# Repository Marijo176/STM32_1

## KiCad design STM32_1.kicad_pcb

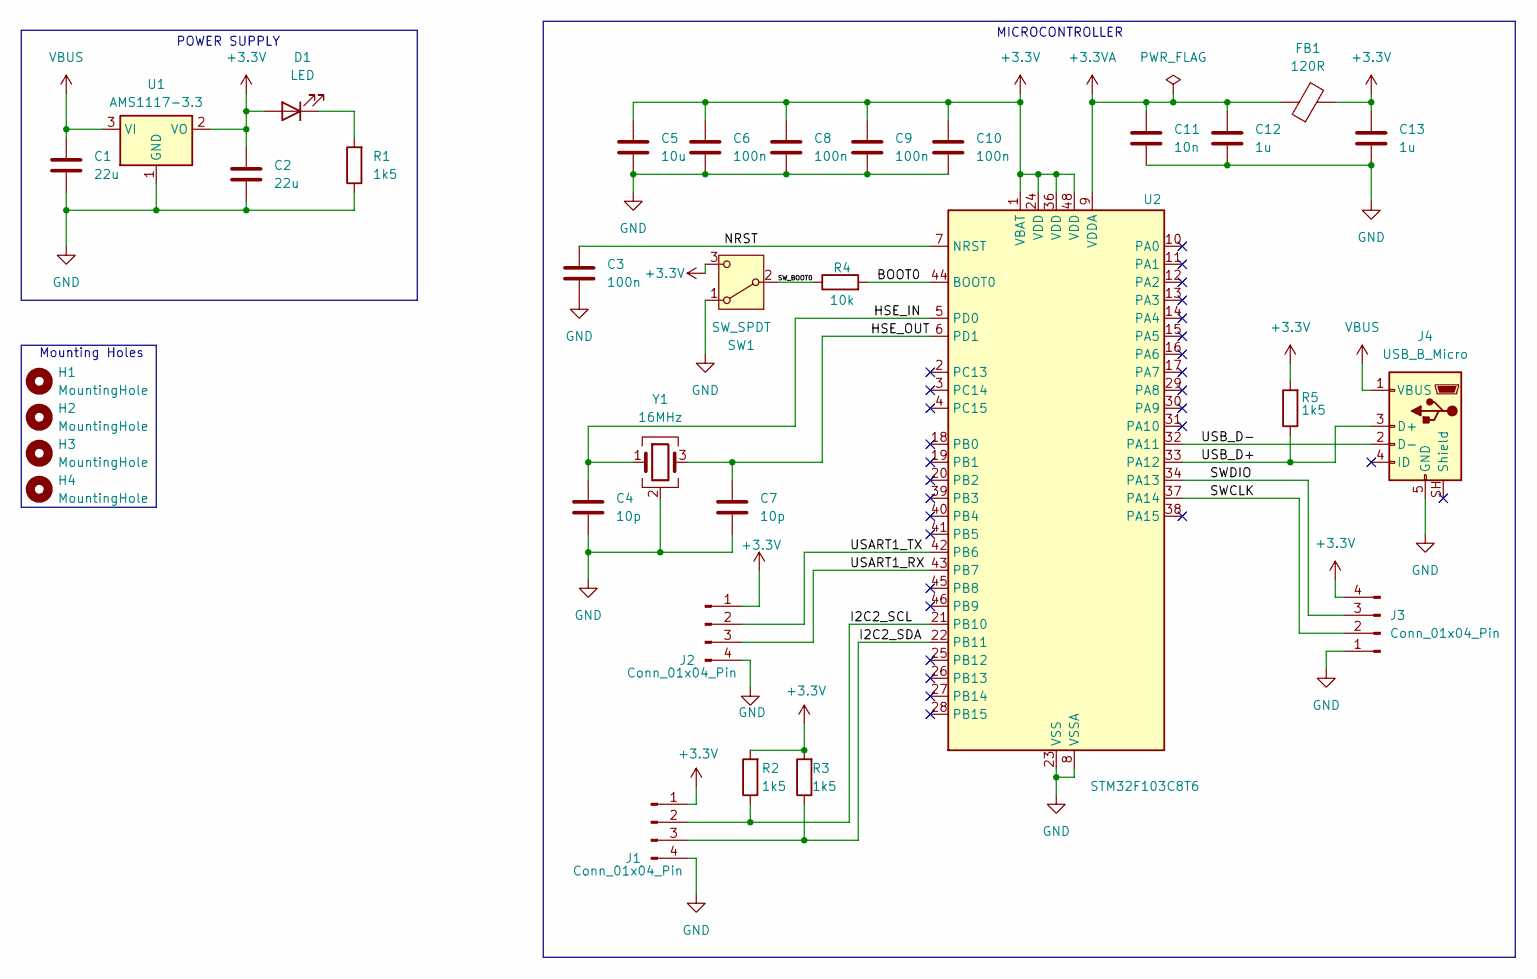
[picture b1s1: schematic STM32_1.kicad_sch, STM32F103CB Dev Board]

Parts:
C1, C2: 22u; C_0805_2012Metric
C3, C6, C8, C9, C10: 100n; C_0402_1005Metric
C4, C7: 10p; C_0402_1005Metric
C5: 10u; C_0603_1608Metric
C11: 10n; C_0402_1005Metric
C12, C13: 1u; C_0402_1005Metric
D1: LED; LED_0603_1608Metric
FB1: 120R; L_0603_1608Metric
H1, H2, H3, H4: MountingHole; MountingHole_2.2mm_M2
J1, J2, J3: Conn_01x04_Pin; PinHeader_1x04_P2.54mm_Vertical
J4: USB_B_Micro; USB_Micro-B_Wuerth_629105150521
R1, R2, R3, R5: 1k5; R_0402_1005Metric
R4: 10k; R_0402_1005Metric
SW1: SW_SPDT; SW_SPDT_PCM12
U1: AMS1117-3.3; SOT-223-3_TabPin2
U2: STM32F103C8T6; LQFP-48_7x7mm_P0.5mm
Y1: 16MHz; Crystal_SMD_3225-4Pin_3.2x2.5mm

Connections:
+3.3V: C2.1, C5.1, C6.1, C8.1, C9.1, C10.1, C13.1, D1.2 (A), FB1.2, J1.1, J2.1, J3.4, R2.2, R3.2, R5.2, SW1.3 (C), U1.2 (VO), U2.1 (VBAT), U2.24 (VDD), U2.36 (VDD), U2.48 (VDD)
+3.3VA: C11.1, C12.1, FB1.1, U2.9 (VDDA)
/BOOT0: R4.2, U2.44 (BOOT0)
/HSE_IN: C4.1, U2.5 (PD0), Y1.1
/HSE_OUT: C7.1, U2.6 (PD1), Y1.3
/I2C2_SCL: J1.2, R2.1, U2.21 (PB10)
/I2C2_SDA: J1.3, R3.1, U2.22 (PB11)
/NRST: C3.1, U2.7 (NRST)
/SWCLK: J3.2, U2.37 (PA14)
/SWDIO: J3.3, U2.34 (PA13)
/SW_BOOT0: R4.1, SW1.2 (B)
/USART1_RX: J2.3, U2.43 (PB7)
/USART1_TX: J2.2, U2.42 (PB6)
/USB_D+: J4.3 (D+), R5.1, U2.33 (PA12)
/USB_D-: J4.2 (D-), U2.32 (PA11)
GND: C1.2, C2.2, C3.2, C4.2, C5.2, C6.2, C7.2, C8.2, C9.2, C10.2, C11.2, C12.2, C13.2, J1.4, J2.4, J3.1, J4.5 (GND), R1.1, SW1.1 (A), U1.1 (GND), U2.8 (VSSA), U2.23 (VSS), U2.35 (VSS), U2.47 (VSS), Y1.2 (G), Y1.4 (G)
unnamed: D1.1 (K), R1.2
VBUS: C1.1, J4.1 (VBUS), U1.3 (VI)

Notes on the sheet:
Mounting Holes
POWER SUPPLY
MICROCONTROLLER

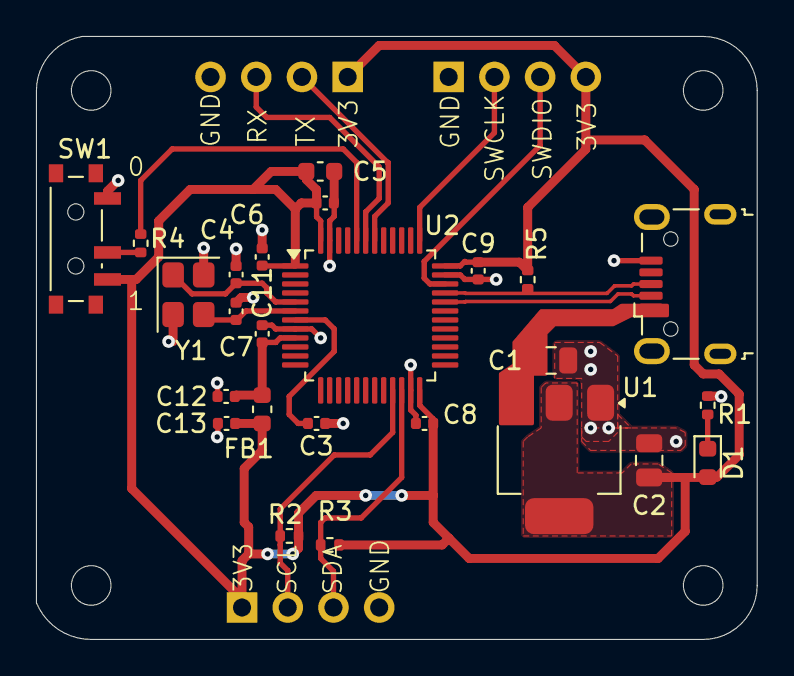
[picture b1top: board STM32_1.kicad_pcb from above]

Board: 2 copper layers, 40.0 x 33.5 mm, 32 parts (0 on the bottom side), 18 nets.
